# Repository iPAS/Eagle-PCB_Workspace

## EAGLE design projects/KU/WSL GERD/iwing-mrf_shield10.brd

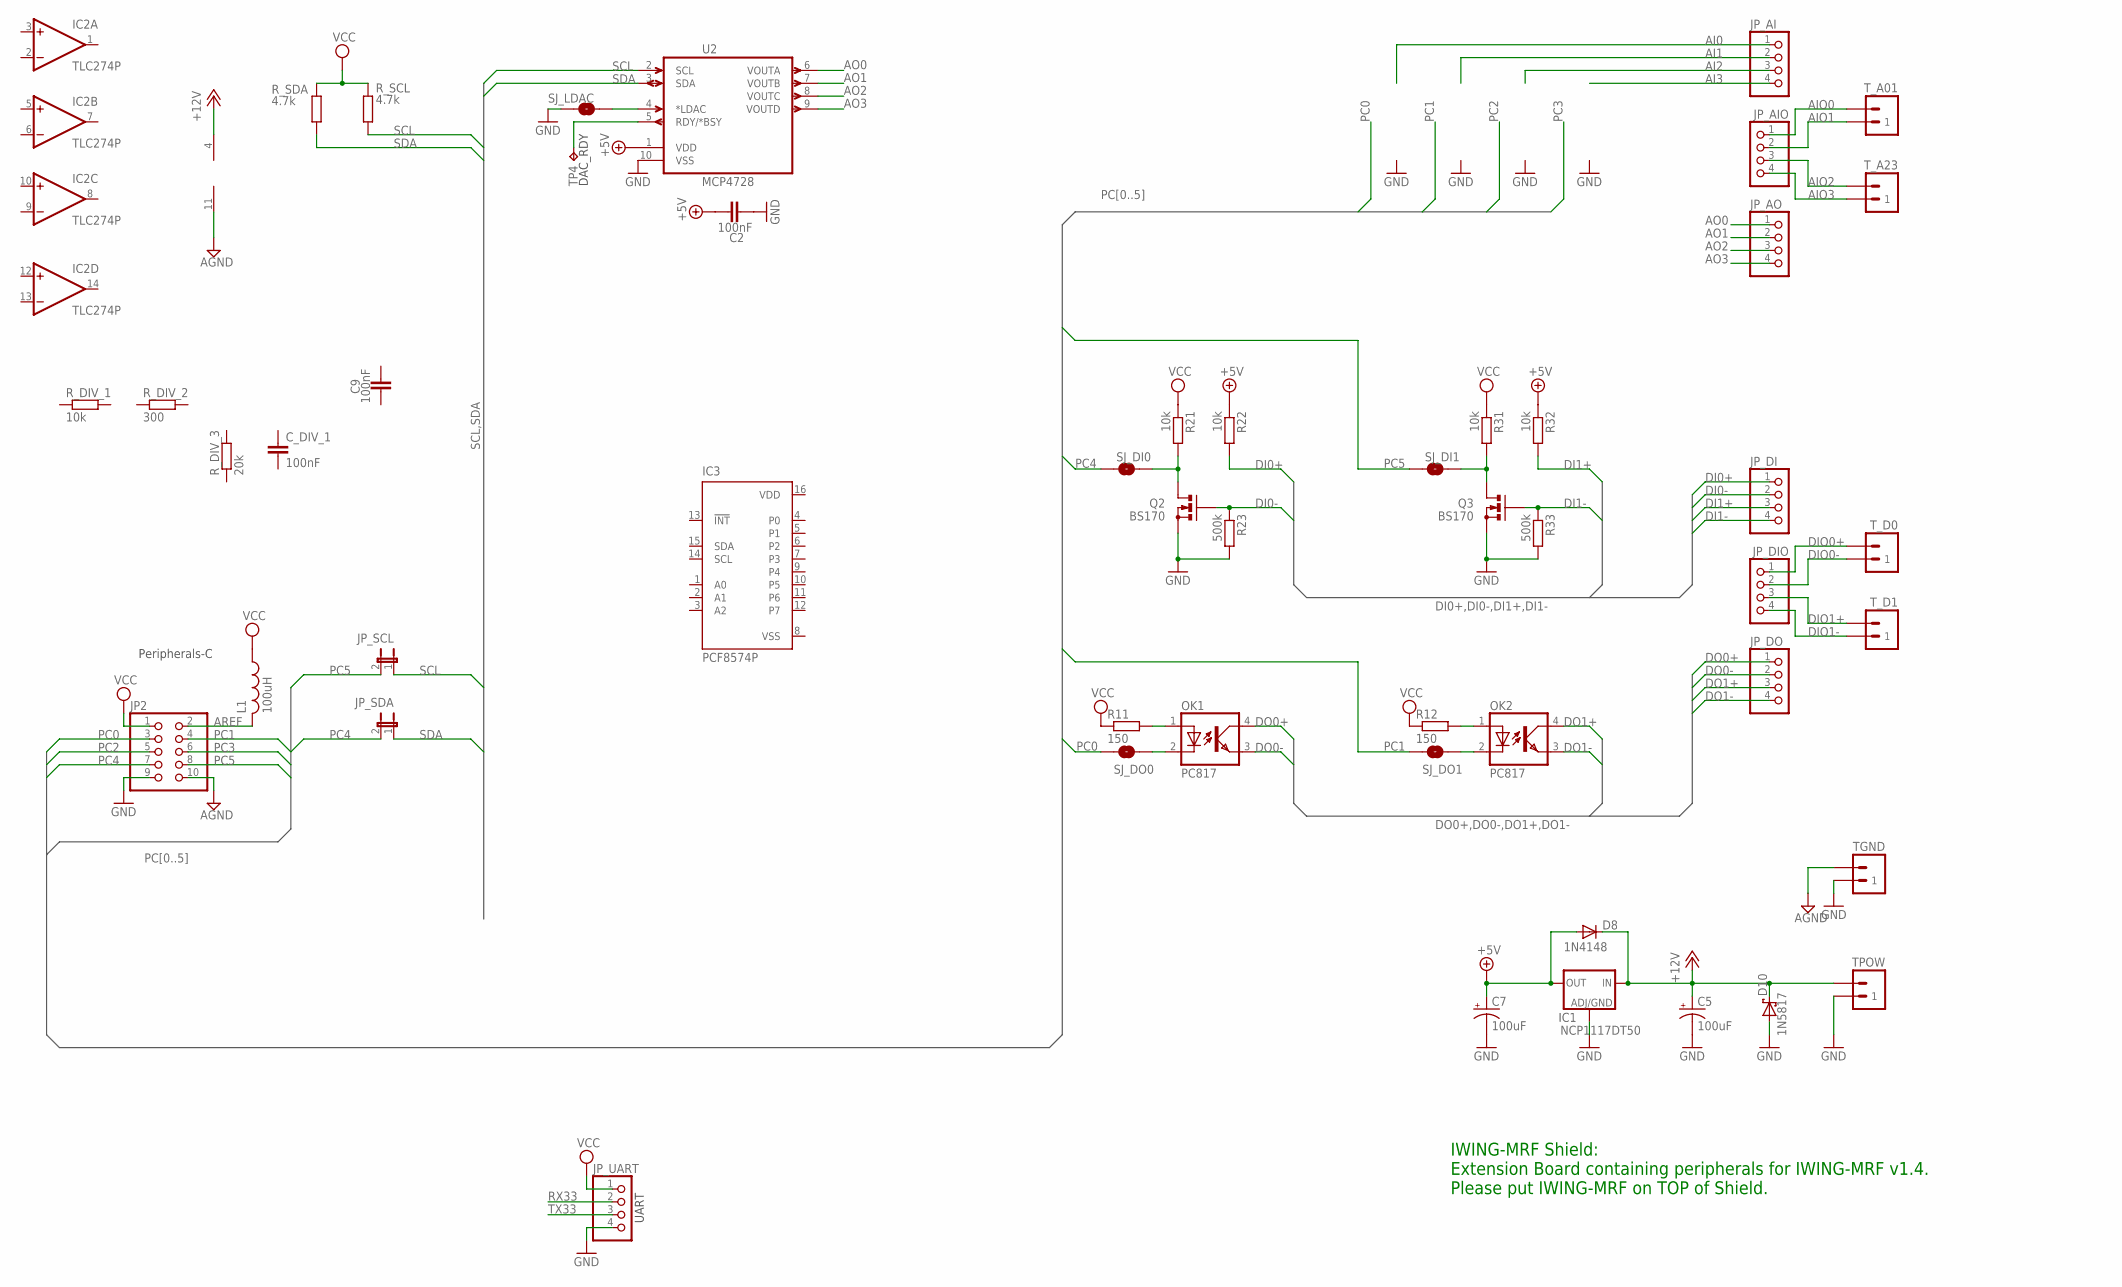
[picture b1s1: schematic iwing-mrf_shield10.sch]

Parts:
C2, C9: 100nF; RCL_C050-025X075
C5, C7: 100uF; RCL_E2,5-7
C_DIV_1: 100nF; RCL_C050-025X075
D8: 1N4148; DO35-100V
D10: 1N5817; DO41-150V
IC1: NCP1117DT50; DPACK
IC2: TLC274P; DIL14
IC3: PCF8574P; DIL16
JP2: HEADER-2X5; 2X05
JP_AI: HEADER-1X4ROUND; 1X04_ROUND
JP_AIO: HEADER-1X4ROUND; 1X04_ROUND
JP_AO: HEADER-1X4ROUND; 1X04_ROUND
JP_DI: HEADER-1X4ROUND; 1X04_ROUND
JP_DIO: HEADER-1X4ROUND; 1X04_ROUND
JP_DO: HEADER-1X4ROUND; 1X04_ROUND
JP_SCL: JUMPER-2SMD-NO; SJ_2S-NO
JP_SDA: JUMPER-2SMD-NO; SJ_2S-NO
JP_UART: HEADER-1X4ROUND; 1X04_ROUND
L1: 100uH; 0204/5
OK1, OK2: PC817; DIL04
Q2, Q3: BS170; TO92-
R11, R12: 150; 0204/5
R21, R22, R31, R32: 10k; 0204/5
R23, R33: 500k; 0204/5
R_DIV_1: 10k; 0204/5
R_DIV_2: 300; 0204/5
R_DIV_3: 20k; 0204/5
R_SCL: 4.7k; 0204/5
R_SDA: 4.7k; 0204/5
SJ_DI0, SJ_DI1: SOLDERJUMPERNO; SJ_2S-NO
SJ_DO0, SJ_DO1: SOLDERJUMPERNO; SJ_2S-NO
SJ_LDAC: SOLDERJUMPERNO; SJ_2S-NO
TGND: ST02-5MM; EK500V-02P
TP4: TPPAD1-13; P1-13
TPOW: ST02-5MM; EK500V-02P
T_A01, T_A23: ST02-5MM; EK500V-02P
T_D0, T_D1: ST02-5MM; EK500V-02P
U2: MCP4728; MSOP-10

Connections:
+5V: C2.1, C7.+, D8.A, IC1.4 (OUT), R22.1, R32.1, U2.1 (VDD)
+12V: C5.+, D8.C, D10.C, IC1.3 (IN), IC2.4 (V+), TPOW.P$2 (2)
AGND: IC2.11 (V-), JP2.10, TGND.P$2 (2)
AI0: JP_AI.1
AI1: JP_AI.2
AI2: JP_AI.3
AI3: JP_AI.4
AIO0: JP_AIO.1, T_A01.P$2 (2)
AIO1: JP_AIO.2, T_A01.P$1 (1)
AIO2: JP_AIO.3, T_A23.P$2 (2)
AIO3: JP_AIO.4, T_A23.P$1 (1)
AO0: JP_AO.1, U2.6 (VOUTA)
AO1: JP_AO.2, U2.7 (VOUTB)
AO2: JP_AO.3, U2.8 (VOUTC)
AO3: JP_AO.4, U2.9 (VOUTD)
AREF: JP2.2, L1.2
DI0+: JP_DI.1, R22.2
DI0-: JP_DI.2, Q2.2 (G), R23.1
DI1+: JP_DI.3, R32.2
DI1-: JP_DI.4, Q3.2 (G), R33.1
DIO0+: JP_DIO.1, T_D0.P$2 (2)
DIO0-: JP_DIO.2, T_D0.P$1 (1)
DIO1+: JP_DIO.3, T_D1.P$2 (2)
DIO1-: JP_DIO.4, T_D1.P$1 (1)
DO0+: JP_DO.1, OK1.4 (COL)
DO0-: JP_DO.2, OK1.3 (EMIT)
DO1+: JP_DO.3, OK2.4 (COL)
DO1-: JP_DO.4, OK2.3 (EMIT)
GND: C2.2, C5.-, C7.-, D10.A, IC1.1 (ADJ), JP2.9, JP_UART.4, Q2.3 (S), Q3.3 (S), R23.2, R33.2, SJ_LDAC.1, TGND.P$1 (1), TPOW.P$1 (1), U2.10 (VSS)
unnamed: TP4.TP, U2.5 (RDY/*BSY)
unnamed: OK2.2 (C), SJ_DO1.2
unnamed: OK1.2 (C), SJ_DO0.2
unnamed: SJ_LDAC.2, U2.4 (*LDAC)
unnamed: Q2.1 (D), R21.2, SJ_DI0.1
unnamed: Q3.1 (D), R31.2, SJ_DI1.1
unnamed: OK1.1 (A), R11.2
unnamed: OK2.1 (A), R12.2
PC0: JP2.3, SJ_DO0.1
PC1: JP2.4, SJ_DO1.1
PC2: JP2.5
PC3: JP2.6
PC4: JP2.7, JP_SDA.2, SJ_DI0.2
PC5: JP2.8, JP_SCL.2, SJ_DI1.2
RX33: JP_UART.2
SCL: JP_SCL.1, R_SCL.2, U2.2 (SCL)
SDA: JP_SDA.1, R_SDA.2, U2.3 (SDA)
TX33: JP_UART.3
VCC: JP2.1, JP_UART.1, L1.1, R11.1, R12.1, R21.1, R31.1, R_SCL.1, R_SDA.1
VDD: IC3.16 (VDD)
VSS: IC3.8 (VSS)

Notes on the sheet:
UART
Peripherals-C
IWING-MRF Shield: Extension Board containing peripherals for IWING-MRF v1.4. Please put IWING-MRF on TOP of Shield.

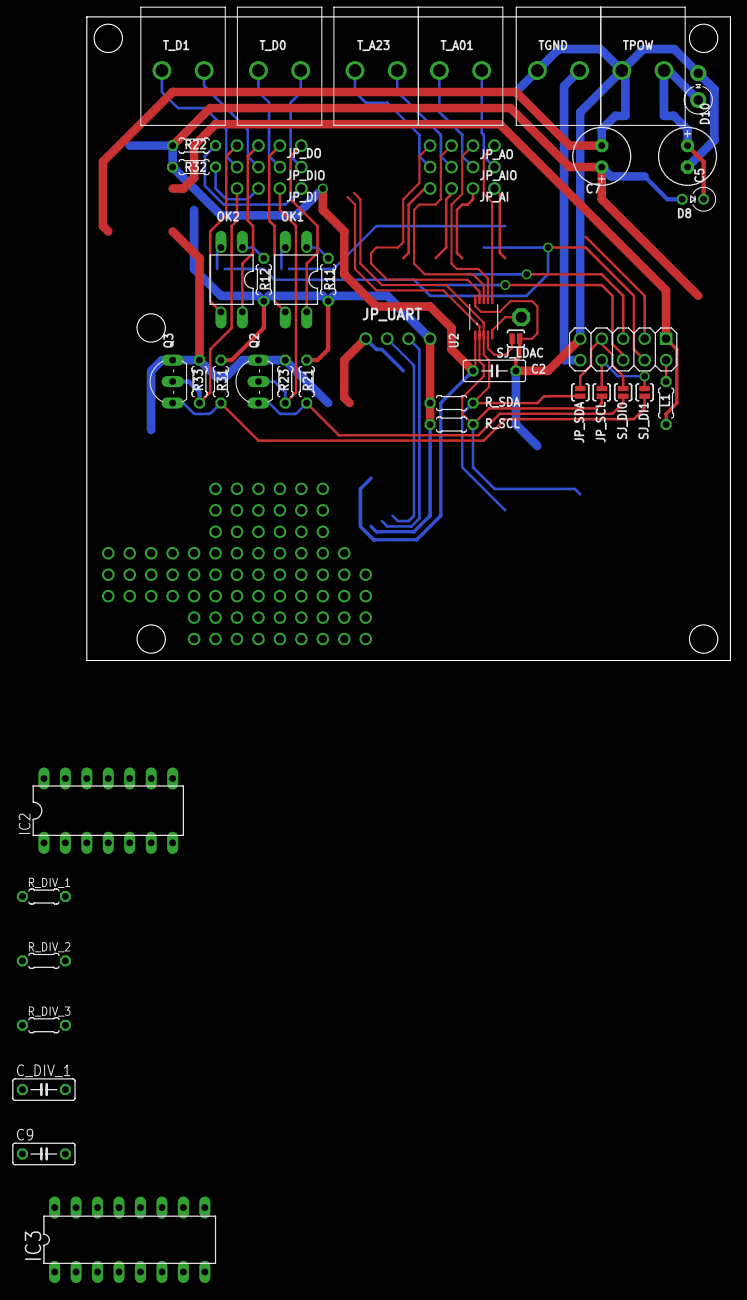
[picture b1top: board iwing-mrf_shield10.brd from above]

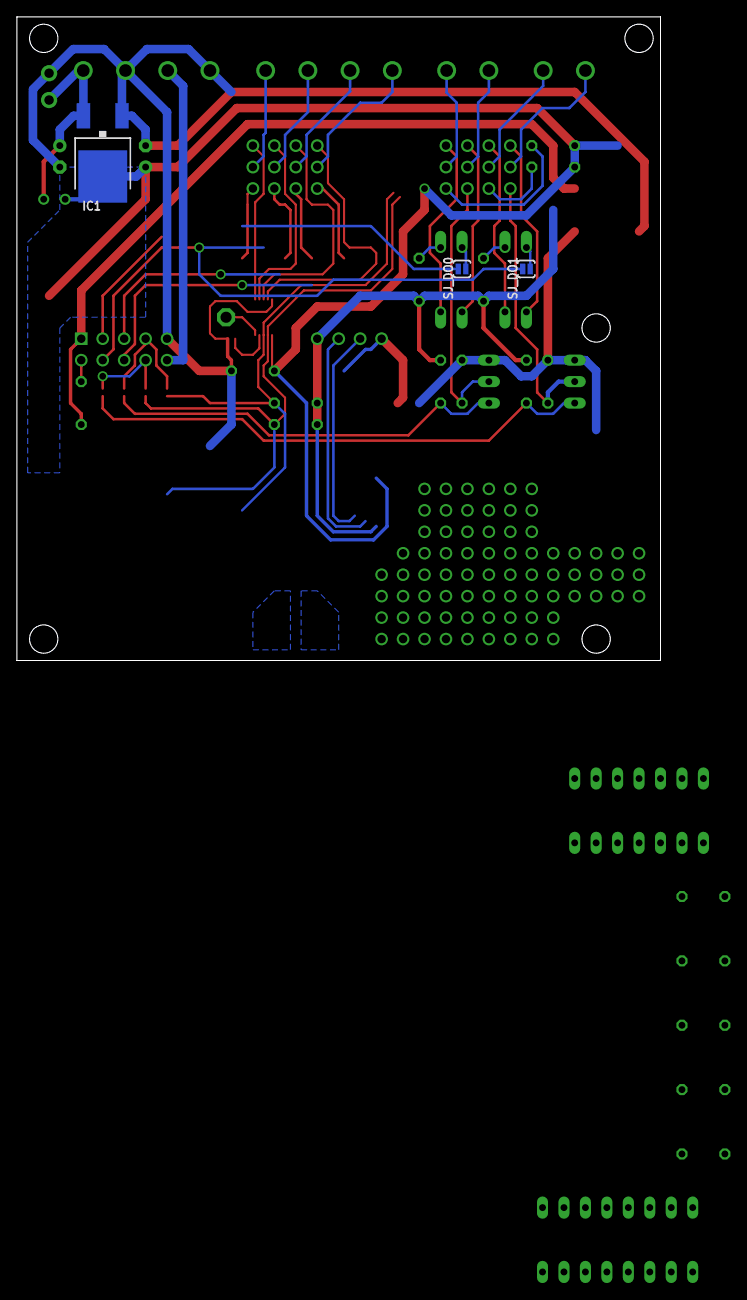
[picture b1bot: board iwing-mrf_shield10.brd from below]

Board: 2 copper layers, 76.2 x 76.2 mm, 51 parts (3 on the bottom side), 40 nets.

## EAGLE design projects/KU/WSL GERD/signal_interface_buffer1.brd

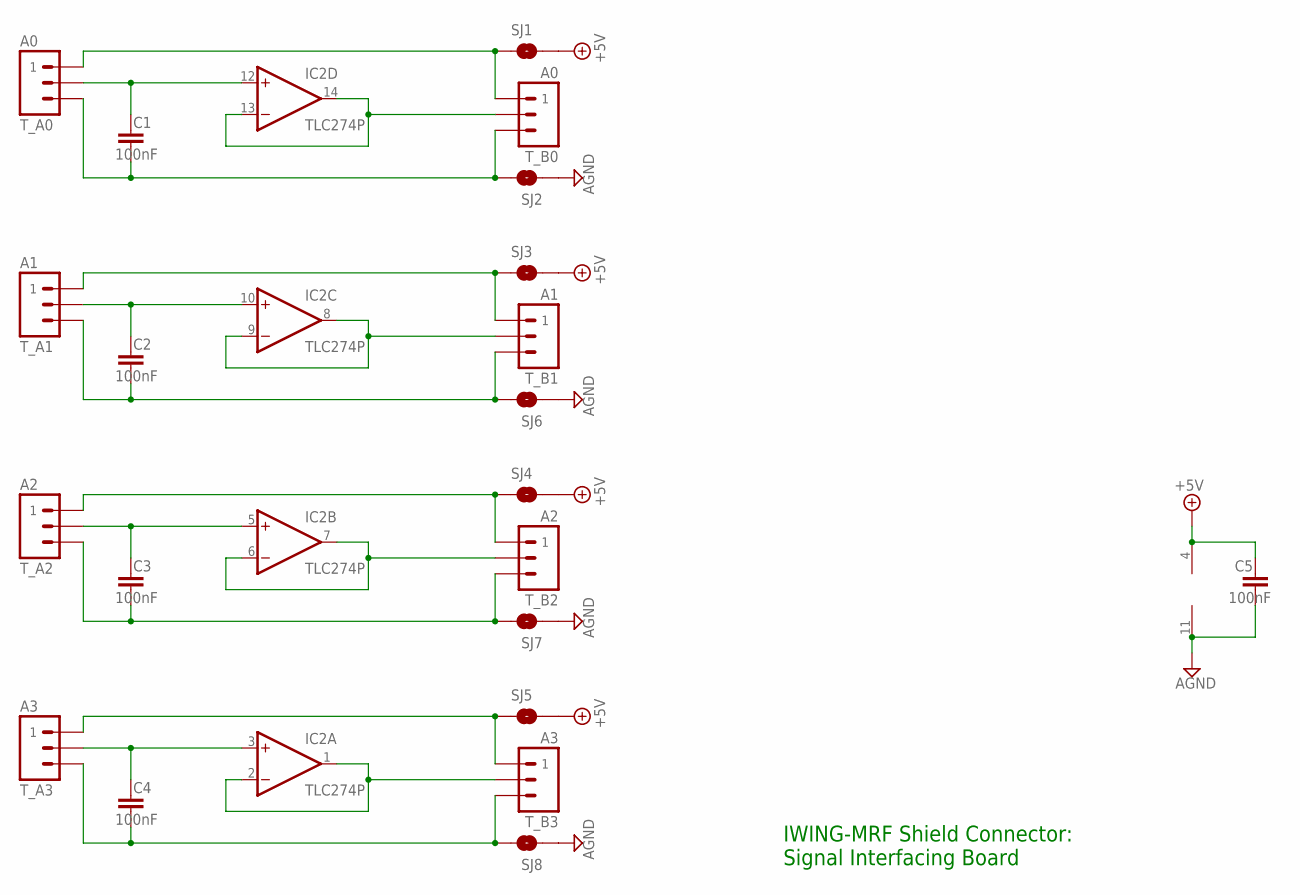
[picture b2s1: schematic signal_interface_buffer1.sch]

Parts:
C1, C2, C3, C4, C5: 100nF; RCL_C050-025X075
IC2: TLC274P; DIL14
SJ1, SJ2, SJ3, SJ4, SJ5, SJ6, SJ7, SJ8: SOLDERJUMPERTRACE; SJ_2S-TRACE
T_A0: A0; ED350V-03P
T_A1: A1; ED350V-03P
T_A2: A2; ED350V-03P
T_A3: A3; ED350V-03P
T_B0: A0; EK500V-03P
T_B1: A1; EK500V-03P
T_B2: A2; EK500V-03P
T_B3: A3; EK500V-03P

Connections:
+5V: C5.1, IC2.4 (V+), SJ1.2, SJ3.2, SJ4.2, SJ5.2
AGND: C5.2, IC2.11 (V-), SJ2.1, SJ6.1, SJ7.1, SJ8.1
AIO0: C1.1, IC2.12 (+IN), T_A0.P$2 (2)
AIO1: C2.1, IC2.10 (+IN), T_A1.P$2 (2)
AIO2: C3.1, IC2.5 (+IN), T_A2.P$2 (2)
unnamed: C4.2, SJ8.2, T_A3.P$3 (3), T_B3.P$3 (3)
unnamed: C3.2, SJ7.2, T_A2.P$3 (3), T_B2.P$3 (3)
unnamed: C2.2, SJ6.2, T_A1.P$3 (3), T_B1.P$3 (3)
unnamed: C1.2, SJ2.2, T_A0.P$3 (3), T_B0.P$3 (3)
unnamed: IC2.13 (-IN), IC2.14 (OUT), T_B0.P$2 (2)
unnamed: IC2.8 (OUT), IC2.9 (-IN), T_B1.P$2 (2)
unnamed: IC2.6 (-IN), IC2.7 (OUT), T_B2.P$2 (2)
unnamed: IC2.1 (OUT), IC2.2 (-IN), T_B3.P$2 (2)
unnamed: SJ1.1, T_A0.P$1 (1), T_B0.P$1 (1)
unnamed: SJ3.1, T_A1.P$1 (1), T_B1.P$1 (1)
unnamed: SJ4.1, T_A2.P$1 (1), T_B2.P$1 (1)
unnamed: SJ5.1, T_A3.P$1 (1), T_B3.P$1 (1)
unnamed: C4.1, IC2.3 (+IN), T_A3.P$2 (2)

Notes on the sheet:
IWING-MRF Shield Connector: Signal Interfacing Board

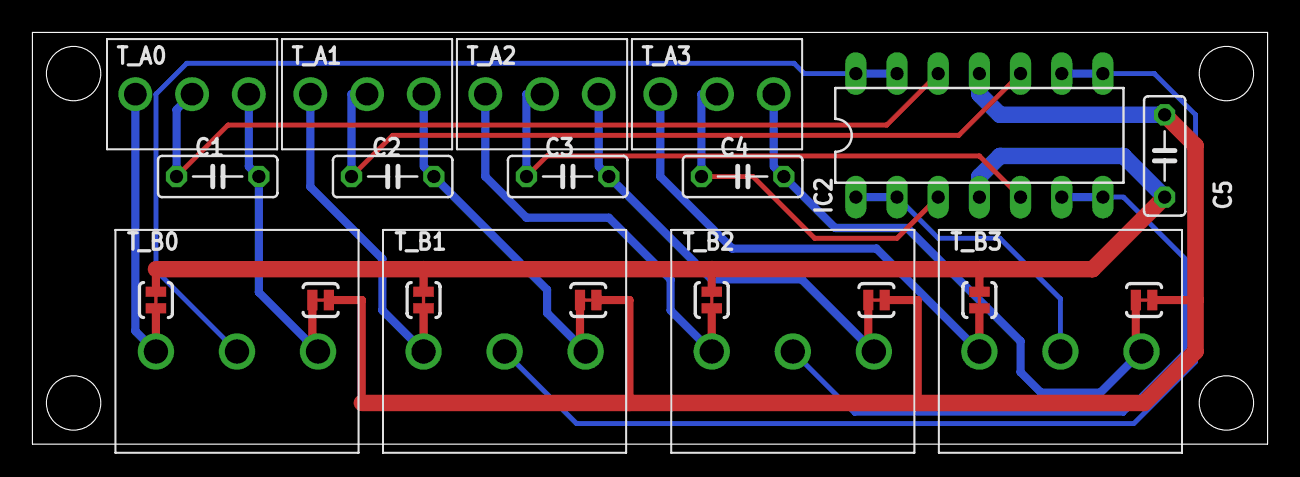
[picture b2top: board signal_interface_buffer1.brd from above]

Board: 2 copper layers, 76.2 x 25.4 mm, 22 parts (0 on the bottom side), 18 nets.

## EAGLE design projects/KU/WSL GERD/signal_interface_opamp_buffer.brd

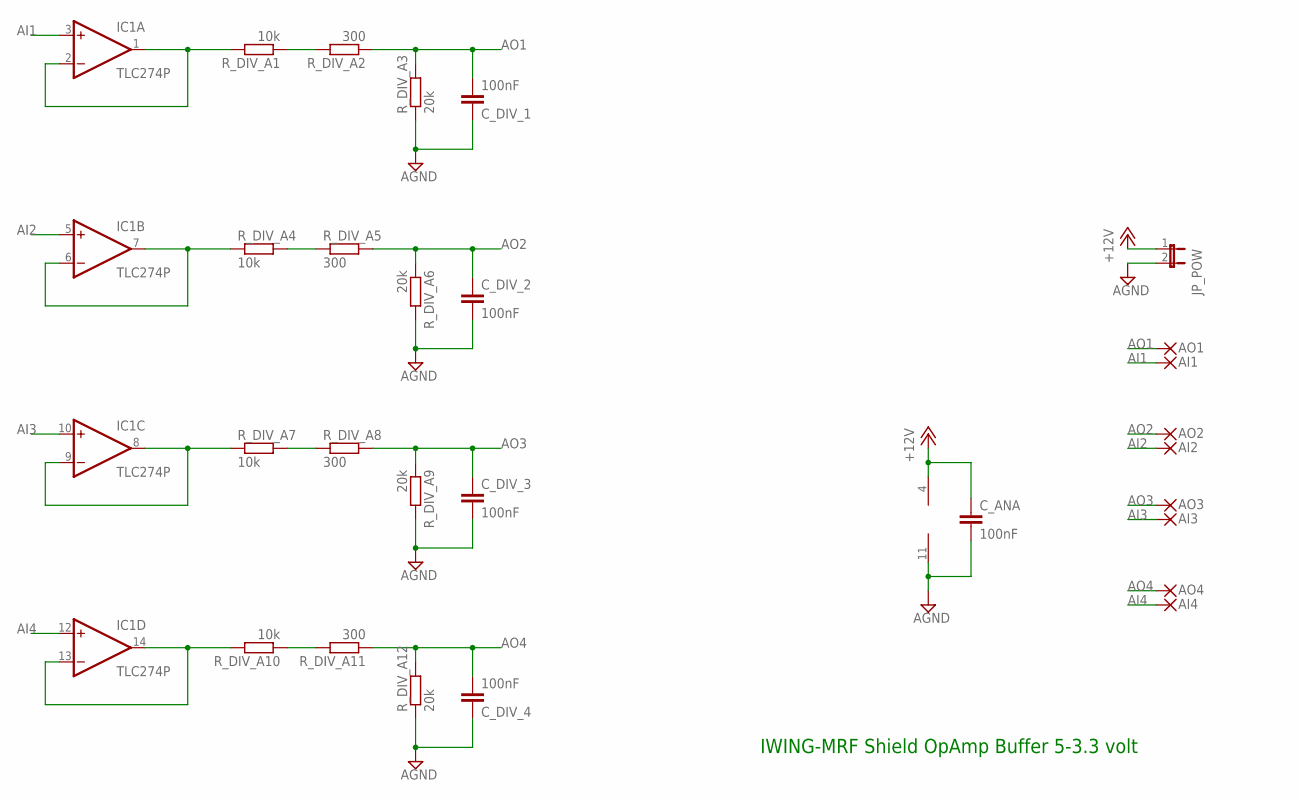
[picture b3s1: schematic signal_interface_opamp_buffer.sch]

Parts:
AI1, AI2, AI3, AI4: WIREPADSMD1,27-254; SMD1,27-2,54
AO1, AO2, AO3, AO4: WIREPADSMD1,27-254; SMD1,27-2,54
C_ANA: 100nF; RCL_C050-025X075
C_DIV_1, C_DIV_2, C_DIV_3, C_DIV_4: 100nF; RCL_C050-025X075
IC1: TLC274P; DIL14
JP_POW: JUMPER-2PTH; 1X02
R_DIV_A1, R_DIV_A4, R_DIV_A7, R_DIV_A10: 10k; 0204V
R_DIV_A2, R_DIV_A5, R_DIV_A8, R_DIV_A11: 300; 0204V
R_DIV_A3, R_DIV_A6, R_DIV_A9, R_DIV_A12: 20k; 0204V

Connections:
+12V: C_ANA.1, IC1.4 (V+), JP_POW.1
AGND: C_ANA.2, C_DIV_1.1, C_DIV_2.2, C_DIV_3.2, C_DIV_4.1, IC1.11 (V-), JP_POW.2, R_DIV_A3.1, R_DIV_A6.2, R_DIV_A9.2, R_DIV_A12.1
AI1: AI1.1, IC1.3 (+IN)
AI2: AI2.1, IC1.5 (+IN)
AI3: AI3.1, IC1.10 (+IN)
AI4: AI4.1, IC1.12 (+IN)
AO1: AO1.1, C_DIV_1.2, R_DIV_A2.1, R_DIV_A3.2
AO2: AO2.1, C_DIV_2.1, R_DIV_A5.2, R_DIV_A6.1
AO3: AO3.1, C_DIV_3.1, R_DIV_A8.2, R_DIV_A9.1
AO4: AO4.1, C_DIV_4.2, R_DIV_A11.1, R_DIV_A12.2
unnamed: IC1.1 (OUT), IC1.2 (-IN), R_DIV_A1.2
unnamed: R_DIV_A4.2, R_DIV_A5.1
unnamed: R_DIV_A1.1, R_DIV_A2.2
unnamed: IC1.6 (-IN), IC1.7 (OUT), R_DIV_A4.1
unnamed: R_DIV_A7.2, R_DIV_A8.1
unnamed: IC1.8 (OUT), IC1.9 (-IN), R_DIV_A7.1
unnamed: R_DIV_A10.1, R_DIV_A11.2
unnamed: IC1.13 (-IN), IC1.14 (OUT), R_DIV_A10.2

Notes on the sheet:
IWING-MRF Shield OpAmp Buffer 5-3.3 volt

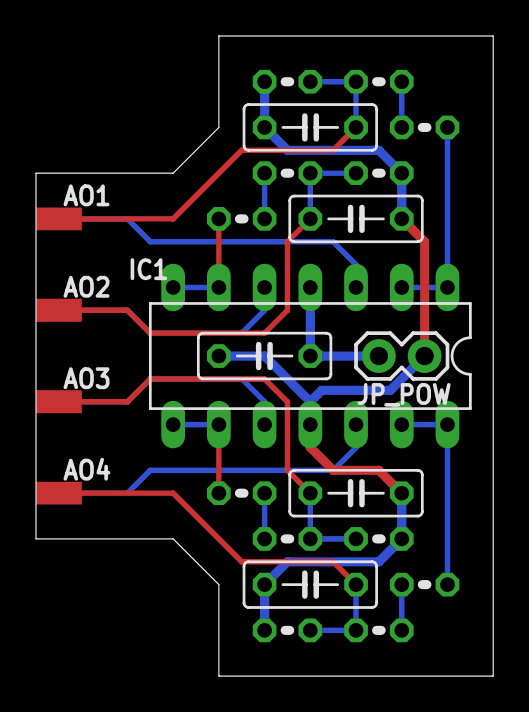
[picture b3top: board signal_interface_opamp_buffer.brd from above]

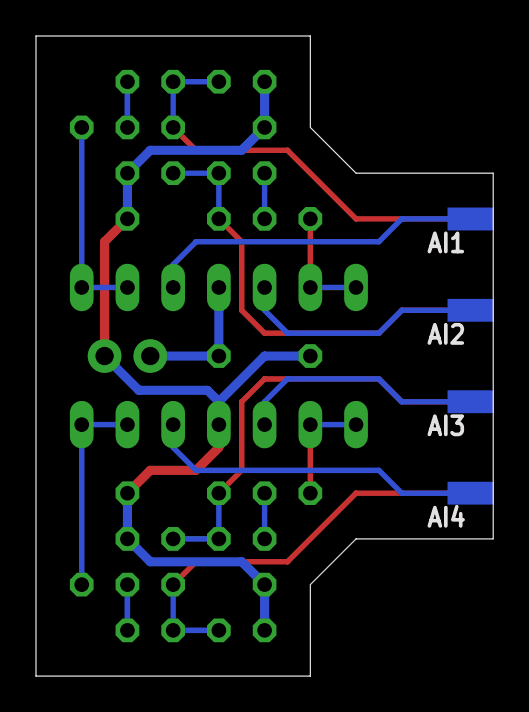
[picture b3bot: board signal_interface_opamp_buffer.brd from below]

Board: 2 copper layers, 25.4 x 35.6 mm, 27 parts (4 on the bottom side), 18 nets.

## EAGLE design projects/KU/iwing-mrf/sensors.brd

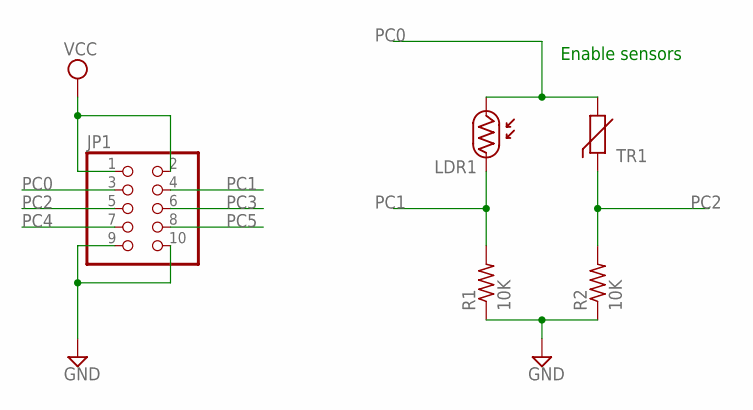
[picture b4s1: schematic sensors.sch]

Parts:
JP1: PINHD-2X5; 2X05
LDR1: LDR; 3MM
R1, R2: 10K; 0204/5
TR1: THERMISTOR_R-5; R-5

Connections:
GND: JP1.9, JP1.10, R1.1, R2.1
PC0: JP1.3, LDR1.P$1, TR1.2
PC1: JP1.4, LDR1.P$2, R1.2
PC2: JP1.5, R2.2, TR1.1
PC3: JP1.6
PC4: JP1.7
PC5: JP1.8
VCC: JP1.1, JP1.2

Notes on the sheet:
Enable sensors

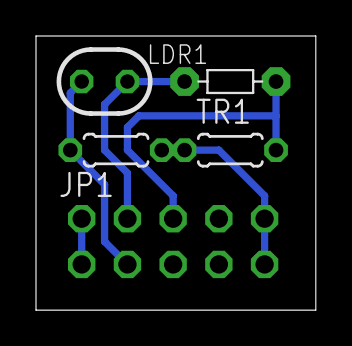
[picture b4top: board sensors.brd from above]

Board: 2 copper layers, 15.5 x 15.2 mm, 5 parts (1 on the bottom side), 5 nets.

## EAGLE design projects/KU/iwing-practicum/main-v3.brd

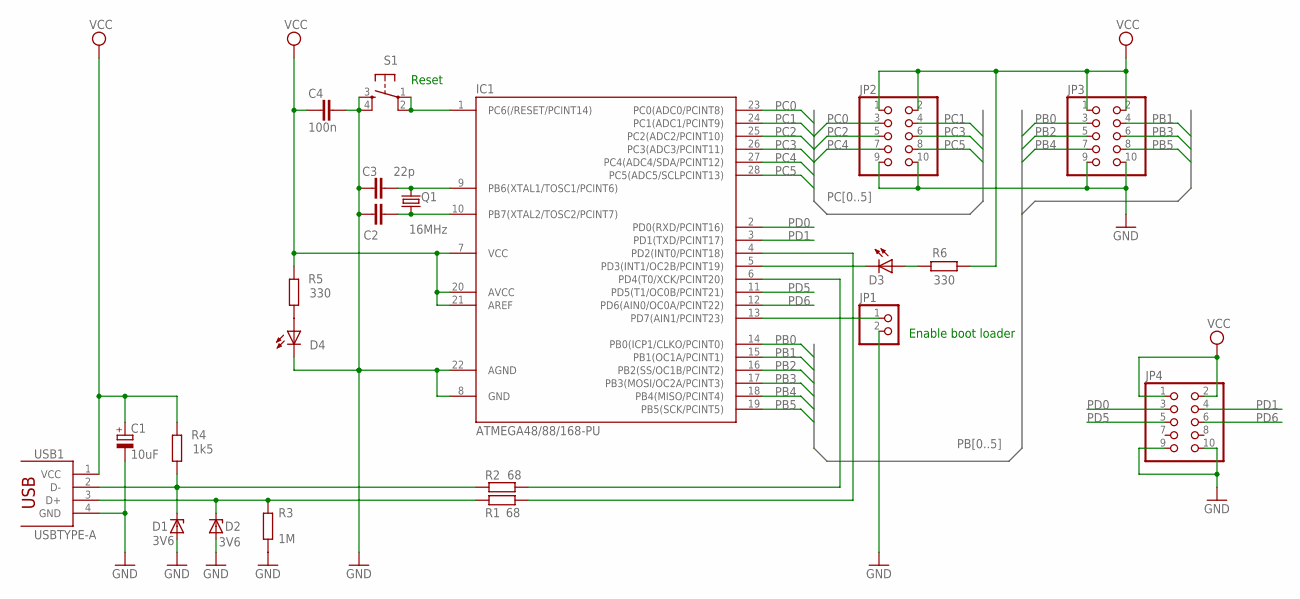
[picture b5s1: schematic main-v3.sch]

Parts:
C1: 10uF; E2,5-6E
C2, C3: 22p; C025-024X044
C4: 100n; C050-024X044
D1, D2: 3V6; DO34Z7
D3, D4: LED3MM
IC1: ATMEGA48/88/168-PU; DIL28-3
JP1: PINHD-1X2; 1X02
JP2, JP3, JP4: HEADER-2X5; 2X05
Q1: 16MHz; HC49/S
R1, R2: 68; 0207/10
R3: 1M; 0207/10
R4: 1k5; 0207/10
R5, R6: 330; 0207/10
S1: DTS-6
USB1: USBTYPE-A

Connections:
D+: D2.C, R1.1, R3.2, USB1.3 (D+)
D-: D1.C, R2.1, R4.2, USB1.2 (D-)
GND: C1.-, C2.1, C3.1, C4.2, D1.A, D2.A, D4.K (C), IC1.8 (GND), IC1.22 (AGND), JP1.2, JP2.9, JP2.10, JP3.9, JP3.10, JP4.9, JP4.10, R3.1, S1.3, S1.4, USB1.4 (GND)
unnamed: IC1.4 (PD2(INT0/PCINT18)), R1.2
unnamed: IC1.1 (PC6(/RESET/PCINT14)), S1.1, S1.2
unnamed: IC1.6 (PD4(T0/XCK/PCINT20)), R2.2
unnamed: IC1.13 (PD7(AIN1/PCINT23)), JP1.1
unnamed: D3.K (C), IC1.5 (PD3(INT1/OC2B/PCINT19))
unnamed: D4.A, R5.2
unnamed: D3.A, R6.2
unnamed: C2.2, IC1.10 (PB7(XTAL2/TOSC2/PCINT7)), Q1.1
unnamed: C3.2, IC1.9 (PB6(XTAL1/TOSC1/PCINT6)), Q1.2
PB0: IC1.14 (PB0(ICP1/CLKO/PCINT0)), JP3.3
PB1: IC1.15 (PB1(OC1A/PCINT1)), JP3.4
PB2: IC1.16 (PB2(SS/OC1B/PCINT2)), JP3.5
PB3: IC1.17 (PB3(MOSI/OC2A/PCINT3)), JP3.6
PB4: IC1.18 (PB4(MISO/PCINT4)), JP3.7
PB5: IC1.19 (PB5(SCK/PCINT5)), JP3.8
PC0: IC1.23 (PC0(ADC0/PCINT8)), JP2.3
PC1: IC1.24 (PC1(ADC1/PCINT9)), JP2.4
PC2: IC1.25 (PC2(ADC2/PCINT10)), JP2.5
PC3: IC1.26 (PC3(ADC3/PCINT11)), JP2.6
PC4: IC1.27 (PC4(ADC4/SDA/PCINT12)), JP2.7
PC5: IC1.28 (PC5(ADC5/SCLPCINT13)), JP2.8
PD0: IC1.2 (PD0(RXD/PCINT16)), JP4.3
PD1: IC1.3 (PD1(TXD/PCINT17)), JP4.4
PD5: IC1.11 (PD5(T1/OC0B/PCINT21)), JP4.5
PD6: IC1.12 (PD6(AIN0/OC0A/PCINT22)), JP4.6
VCC: C1.+, C4.1, IC1.7 (VCC), IC1.20 (AVCC), IC1.21 (AREF), JP2.1, JP2.2, JP3.1, JP3.2, JP4.1, JP4.2, R4.1, R5.1, R6.1, USB1.1 (VCC)

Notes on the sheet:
Enable boot loader
Reset

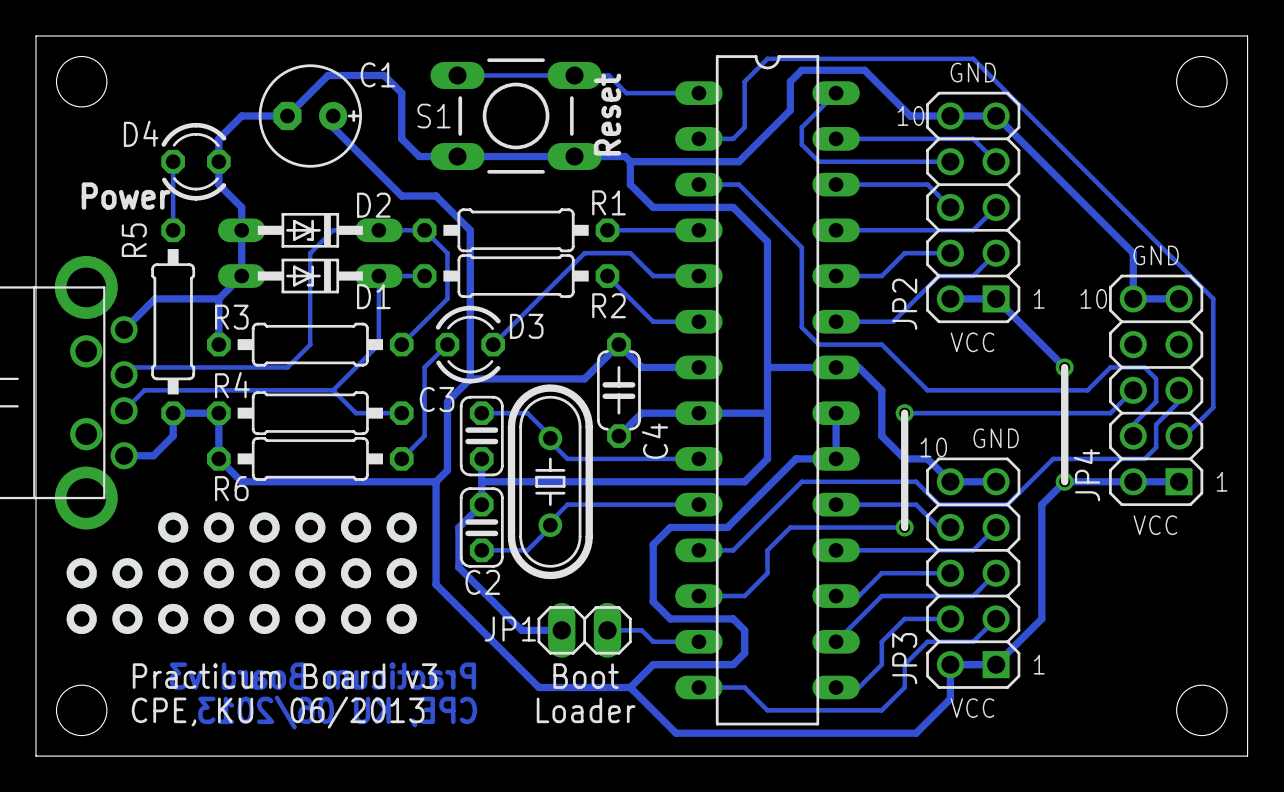
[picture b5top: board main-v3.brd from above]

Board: 2 copper layers, 67.3 x 40.0 mm, 22 parts (0 on the bottom side), 29 nets.

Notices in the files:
parts and their libraries:
SparkFun-Passives: Licensing: CC v3.0 Share-Alike You are welcome to use this library for commercial purposes.
